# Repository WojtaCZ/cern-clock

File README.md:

# CERN CLOCK
This repository contains all the files for the CERN CLOCK project. The [firmware](firmware) folder contains the assembly for the 6809 processor as well as the sources for the RP Pico W. [Hardware](hardware) contains the reverse engineered schematic of the decoder board and the project for the controller board. [Mechanical](mechanical) folder contains the 3D printable parts and outlines for the plexi panels.

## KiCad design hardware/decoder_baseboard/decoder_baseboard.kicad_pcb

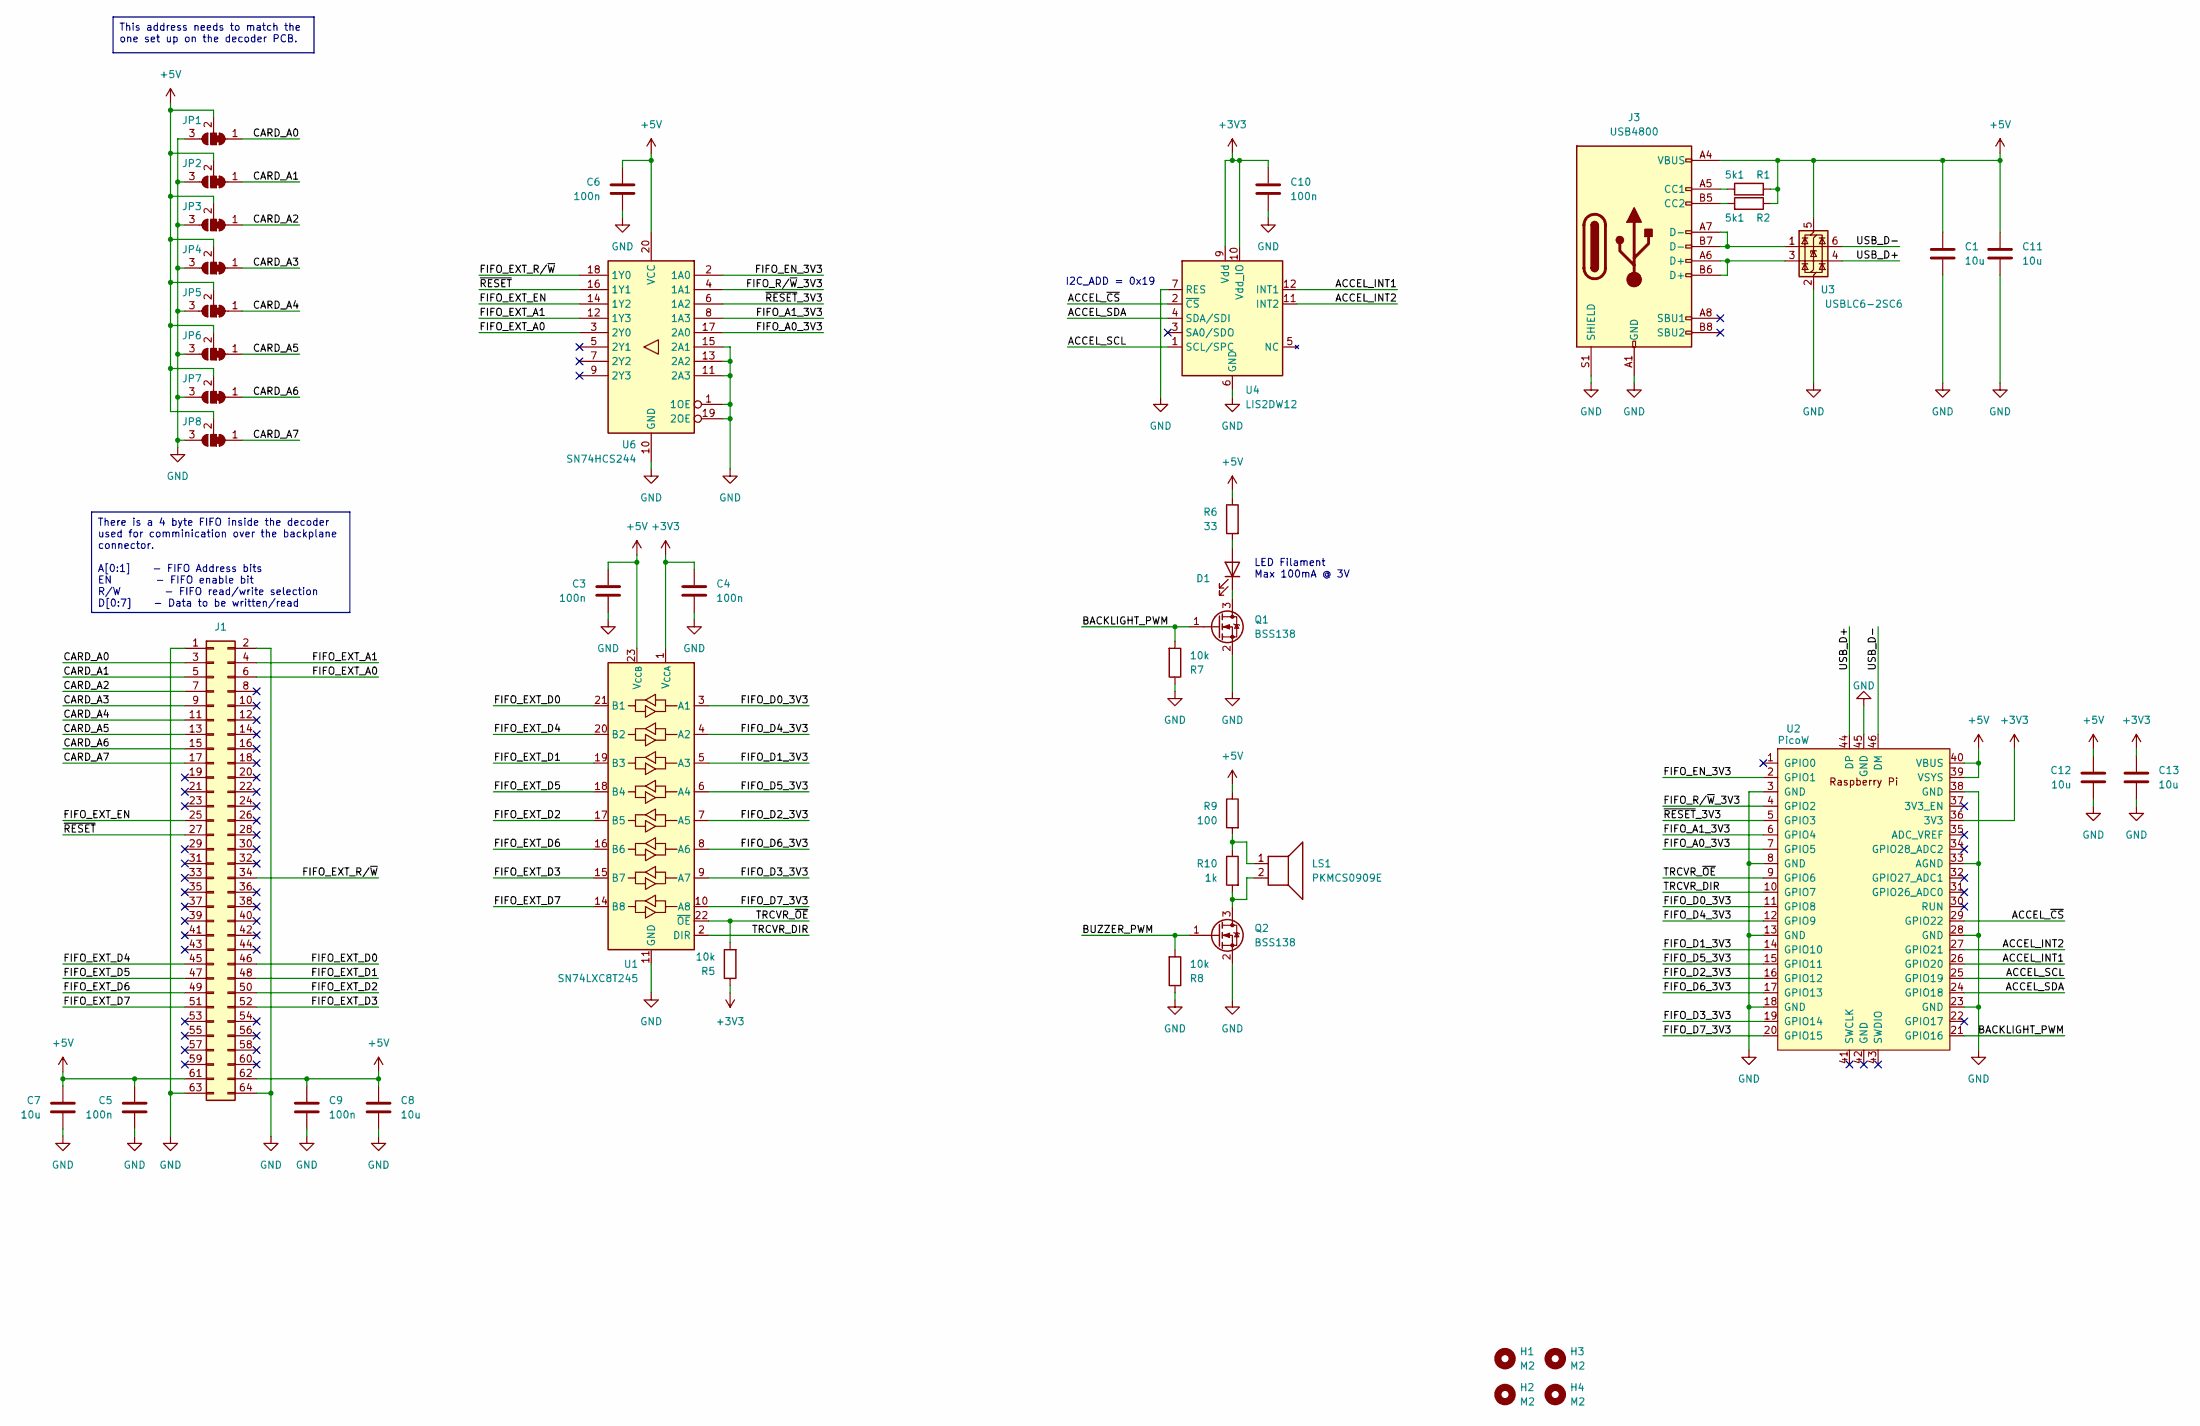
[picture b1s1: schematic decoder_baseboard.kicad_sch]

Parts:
C1, C7, C8, C11, C12, C13: 10u; C_0603_1608Metric
C3, C4, C5, C6, C9, C10: 100n; C_0603_1608Metric
D1: LED FILAMENT; Con_01x02_2.54_SMD
H1, H2, H3, H4: M2; MountingHole_2.5mm
J1: Conn_02x32_Odd_Even; PinSocket_2x32_P2.54mm_Vertical_SMD
J3: USB4800; USB_C_Receptacle_GCT_USB4800
JP1, JP2, JP3, JP4, JP5, JP6, JP7, JP8: SolderJumper_3_Bridged12; SolderJumper-3_P1.3mm_Bridged2Bar12_Pad1.0x1.5mm
LS1: PKMCS0909E; Buzzer_Murata_PKMCS0909E
Q1, Q2: BSS138; SOT-23
R1, R2: 5k1; R_0603_1608Metric
R5, R7, R8: 10k; R_0603_1608Metric
R6: 33; R_0603_1608Metric
R9: 100; R_0603_1608Metric
R10: 1k; R_0603_1608Metric
U1: SN74LXC8T245; TSSOP-24_4.4x7.8mm_P0.65mm
U2: PicoW; RPi_Pico_SMD_TH
U3: USBLC6-2SC6; SOT-23-6
U4: LIS2DW12; LGA-12_2x2mm_P0.5mm
U6: SN74HCS244; TSSOP-20_4.4x6.5mm_P0.65mm

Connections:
+3V3: C4.1, C10.1, C13.1, R5.1, U1.1 (V_{CCA}), U2.36 (3V3), U4.9 (Vdd), U4.10 (Vdd_IO)
+5V: C1.1, C3.1, C5.1, C6.1, C7.1, C8.1, C9.1, C11.1, C12.1, J1.61, J1.62, J3.A4 (VBUS), J3.A9 (VBUS), J3.B4 (VBUS), J3.B9 (VBUS), JP1.2 (C), JP2.2 (C), JP3.2 (C), JP4.2 (C), JP5.2 (C), JP6.2 (C), JP7.2 (C), JP8.2 (C), R1.2, R2.1, R6.1, R9.1, U1.23 (V_{CCB}), U1.24 (V_{CCB}), U2.39 (VSYS), U2.40 (VBUS), U3.5 (VBUS), U6.20 (VCC)
/ACCEL_INT1: U2.26 (GPIO20), U4.12 (INT1)
/ACCEL_INT2: U2.27 (GPIO21), U4.11 (INT2)
/ACCEL_SCL: U2.25 (GPIO19), U4.1 (SCL/SPC)
/ACCEL_SDA: U2.24 (GPIO18), U4.4 (SDA/SDI)
/ACCEL_~CS: U2.29 (GPIO22), U4.2 (~CS)
/BACKLIGHT_PWM: Q1.1 (G), R7.2, U2.21 (GPIO16)
/BUZZER_PWM: Q2.1 (G), R8.2
/CARD_A0: J1.3, JP1.1 (A)
/CARD_A1: J1.5, JP2.1 (A)
/CARD_A2: J1.7, JP3.1 (A)
/CARD_A3: J1.9, JP4.1 (A)
/CARD_A4: J1.11, JP5.1 (A)
/CARD_A5: J1.13, JP6.1 (A)
/CARD_A6: J1.15, JP7.1 (A)
/CARD_A7: J1.17, JP8.1 (A)
/FIFO_A0_3V3: U2.7 (GPIO5), U6.17 (2A0)
/FIFO_A1_3V3: U2.6 (GPIO4), U6.8 (1A3)
/FIFO_D0_3V3: U1.3 (A1), U2.11 (GPIO8)
/FIFO_D1_3V3: U1.5 (A3), U2.14 (GPIO10)
/FIFO_D2_3V3: U1.7 (A5), U2.16 (GPIO12)
/FIFO_D3_3V3: U1.9 (A7), U2.19 (GPIO14)
/FIFO_D4_3V3: U1.4 (A2), U2.12 (GPIO9)
/FIFO_D5_3V3: U1.6 (A4), U2.15 (GPIO11)
/FIFO_D6_3V3: U1.8 (A6), U2.17 (GPIO13)
/FIFO_D7_3V3: U1.10 (A8), U2.20 (GPIO15)
/FIFO_EN_3V3: U2.2 (GPIO1), U6.2 (1A0)
/FIFO_EXT_A0: J1.6, U6.3 (2Y0)
/FIFO_EXT_A1: J1.4, U6.12 (1Y3)
/FIFO_EXT_D0: J1.46, U1.21 (B1)
/FIFO_EXT_D1: J1.48, U1.19 (B3)
/FIFO_EXT_D2: J1.50, U1.17 (B5)
/FIFO_EXT_D3: J1.52, U1.15 (B7)
/FIFO_EXT_D4: J1.45, U1.20 (B2)
/FIFO_EXT_D5: J1.47, U1.18 (B4)
/FIFO_EXT_D6: J1.49, U1.16 (B6)
/FIFO_EXT_D7: J1.51, U1.14 (B8)
/FIFO_EXT_EN: J1.25, U6.14 (1Y2)
/FIFO_EXT_R/~W: J1.34, U6.18 (1Y0)
/FIFO_R/~W_3V3: U2.4 (GPIO2), U6.4 (1A1)
/TRCVR_DIR: U1.2 (DIR), U2.10 (GPIO7)
/TRCVR_~OE: R5.2, U1.22 (~OE), U2.9 (GPIO6)
/USB_D+: U2.44 (DP), U3.4 (I/O2)
/USB_D-: U2.46 (DM), U3.6 (I/O1)
/~RESET: J1.27, U6.16 (1Y1)
/~RESET_3V3: U2.5 (GPIO3), U6.6 (1A2)
GND: C1.2, C3.2, C4.2, C5.2, C6.2, C7.2, C8.2, C9.2, C10.2, C11.2, C12.2, C13.2, J1.1, J1.2, J1.63, J1.64, J3.A1 (GND), J3.A12 (GND), J3.B1 (GND), J3.B12 (GND), J3.S1 (SHIELD), JP1.3 (B), JP2.3 (B), JP3.3 (B), JP4.3 (B), JP5.3 (B), JP6.3 (B), JP7.3 (B), JP8.3 (B), Q1.2 (S), Q2.2 (S), R7.1, R8.1, U1.11 (GND), U1.12 (GND), U1.13 (GND), U2.3 (GND), U2.8 (GND), U2.13 (GND), U2.18 (GND), U2.23 (GND), U2.28 (GND), U2.33 (AGND), U2.38 (GND), U2.45 (GND), U3.2 (GND), U4.6 (GND), U4.7 (RES), U4.8 (GND), U6.1 (1OE), U6.10 (GND), U6.11 (2A3), U6.13 (2A2), U6.15 (2A1), U6.19 (2OE)
unnamed: D1.2 (A), R6.2
unnamed: D1.1 (K), Q1.3 (D)
unnamed: J3.A5 (CC1), R1.1
unnamed: J3.B5 (CC2), R2.2
unnamed: J3.A6 (D+), J3.B6 (D+), U3.3 (I/O2)
unnamed: J3.A7 (D-), J3.B7 (D-), U3.1 (I/O1)
unnamed: LS1.1, R9.2, R10.1
unnamed: LS1.2, Q2.3 (D), R10.2

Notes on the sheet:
This address needs to match the one set up on the decoder PCB.
There is a 4 byte FIFO inside the decoder used for comminication over the backplane connector. A[0:1] - FIFO Address bits EN - FIFO enable bit R/W - FIFO read/write selection D[0:7] - Data to be written/read
I2C_ADD = 0x19
LED Filament Max 100mA @ 3V

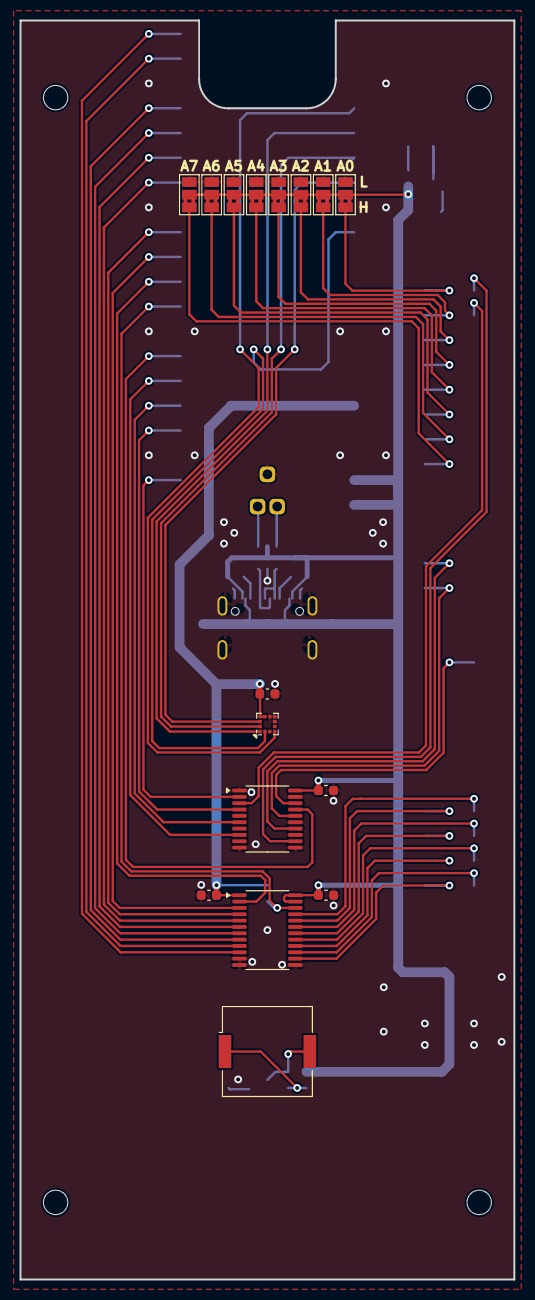
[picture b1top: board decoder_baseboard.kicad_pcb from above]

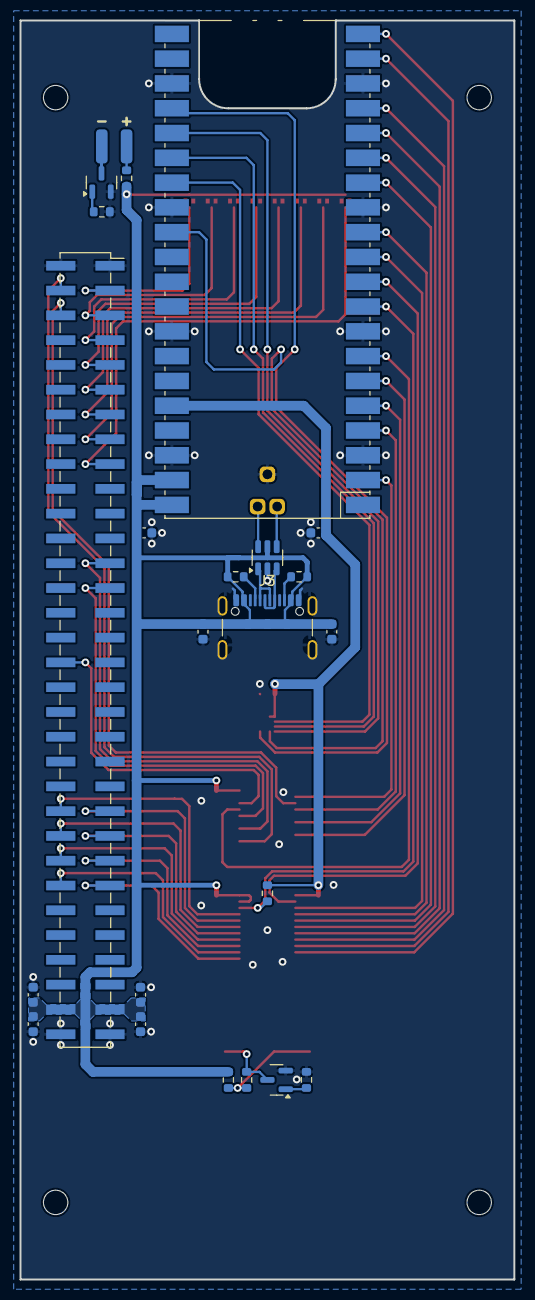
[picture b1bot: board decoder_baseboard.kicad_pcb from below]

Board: 2 copper layers, 50.6 x 129.0 mm, 43 parts (23 on the bottom side), 56 nets.

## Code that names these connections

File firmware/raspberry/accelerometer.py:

from machine import Pin
from machine import I2C
from machine import Timer
import time
import buzzer
import clock
import configuration
import ntp
import logging
logger = logging.getLogger(__name__)

tapCounterInternal = 0
tapCounter = 0
tapFlag = False
tapTimer = None

# Accelerometer interface
ACCEL_CSn		 = Pin(22, Pin.OUT, value=1)
ACCEL_INT1		 = Pin(20, Pin.IN)
ACCEL_INT2		 = Pin(21, Pin.IN)
ACCEL_SDA		 = Pin(18, Pin.PULL_UP)
ACCEL_SCL		 = Pin(19, Pin.PULL_UP)
ACCEL_I2C = I2C(1, freq=100000, scl=ACCEL_SCL, sda=ACCEL_SDA)
ACCEL_I2C_ADD = 25

overrideSleep = False

# Handle the finished tap procedure
def tapHandler(p):
    global tapCounterInternal, tapCounter, tapTimer, tapFlag
    
    # Kill the timer
    if tapTimer != None:
        tapTimer.deinit()
    
    # Update the vars
    tapCounter = tapCounterInternal
    tapCounterInternal = 0

    # Signal a finished tap for processing
    tapFlag = True
        
# If the tap interrupt was received
def int1_handler(p):
    global tapTimer, tapCounterInternal, overrideSleep
    
    # Beep
    buzzer.beep(600, 50)
    
    # Increase the tap count
    tapCounterInternal += 1

    # If the clock is not sleeping, behave ike a screen change
    timeNow = ntp.localTime()

    if (not clock.shouldSleep(timeNow)) or overrideSleep:
        # If it is the first tap, start a timer to wait for the possible second tap
        if tapCounterInternal == 1:
            tapTimer = Timer(period=600, mode=Timer.ONE_SHOT, callback=tapHandler)
        else:
            # Kill the timer and handle the taps
            if tapTimer != None:
                tapTimer.deinit()
            tapHandler(0)

    # But if it is sleeping, wake it up
    else:
        clock.wakeUp()
        return
    
# Set up the accel
def init():
    logger.debug("Initializing the accelerometer")
    
    if ACCEL_I2C.readfrom_mem(ACCEL_I2C_ADD, 0x0F, 1)[0] != 0x44:
        raise Exception("Wrong accelerometer ID!")
    
    logger.debug("Accelerometer detected. Setting up tap detection")
    
    # Set FS to 2g & enable lownoise
    ACCEL_I2C.writeto_mem(ACCEL_I2C_ADD, 0x25, b'\x04')
    # Tap detect routed to INT1
    ACCEL_I2C.writeto_mem(ACCEL_I2C_ADD, 0x23, b'\x40')
    
    # Tap tresholds & enabling
    tapEnableBits = 0; 
    tapEnabled = configuration.read("tap_enable_x");
    print(tapEnabled)
            
    if tapEnabled == "true":
        tapEnableBits |= 0x80
        logger.debug("Tap detection on X axis enabled.")
        try:
            tapTreshold = int(configuration.read("tap_treshold_x"))

            if tapTreshold > 31 or tapTreshold < 0:
                logger.warning("Tap treshold for X axis is out of limits, it will be constrained to comply with the limits")
                tapTreshold = max(min(31, tapTreshold, 0))
            
            logger.debug("Setting tap treshold for X axis to " + str(tapTreshold))
            ACCEL_I2C.writeto_mem(ACCEL_I2C_ADD, 0x30, tapTreshold.to_bytes(1))
        except:
            logger.warning("Tap treshold for X axis has not been found, even though tap detection is enabled. Setting to treshold 6")
            ACCEL_I2C.writeto_mem(ACCEL_I2C_ADD, 0x30, b'\x06')
    else:
        logger.debug("Tap detection on X axis disabled")
    
    tapEnabled = configuration.read("tap_enable_y")
     
    if tapEnabled == "true":
        tapEnableBits |= 0x40
        logger.debug("Tap detection on Y axis enabled")
        try:
            tapTreshold = int(configuration.read("tap_treshold_y"))
            
            if tapTreshold > 31 or tapTreshold < 0:
                logger.warning("Tap treshold for Y axis is out of limits, it will be constrained to comply with the limits")
                tapTreshold = max(min(31, tapTreshold, 0))
            
            logger.debug("Setting tap treshold for Y axis to " + str(tapTreshold))
            ACCEL_I2C.writeto_mem(ACCEL_I2C_ADD, 0x31, tapTreshold.to_bytes(1))
        except:
            logger.warning("Tap treshold for Y axis has not been found, even though tap detection is enabled. Setting to treshold 6")
            ACCEL_I2C.writeto_mem(ACCEL_I2C_ADD, 0x31, b'\x06')  
    else:
        logger.debug("Tap detection on Y axis disabled")
            
    tapEnabled = configuration.read("tap_enable_z")
    
    if tapEnabled == "true":
        tapEnableBits |= 0x20
        logger.debug("Tap detection on Z axis enabled.")
        try:
            tapTreshold = int(configuration.read("tap_treshold_z"))
            
            if tapTreshold > 31 or tapTreshold < 0:
                logger.warning("Tap treshold for Z axis is out of limits, it will be constrained to comply with the limits")
                tapTreshold = max(min(31, tapTreshold, 0))
            
            logger.debug("Setting tap treshold for Z axis to " + str(tapTreshold))
            ACCEL_I2C.writeto_mem(ACCEL_I2C_ADD, 0x32, (tapTreshold | tapEnableBits).to_bytes(1))
        except:
            logger.warning("Tap treshold for Z axis has not been found, even though tap detection is enabled. Setting to treshold 6")
            ACCEL_I2C.writeto_mem(ACCEL_I2C_ADD, 0x32,  (6 | tapEnableBits).to_bytes(1))     
    else:
        ACCEL_I2C.writeto_mem(ACCEL_I2C_ADD, 0x32,  tapEnableBits.to_bytes(1))
        logger.debug("Tap detection on Z axis disabled")
    
    # Set shock duration
    ACCEL_I2C.writeto_mem(ACCEL_I2C_ADD, 0x33, b'\x02')
    # Run mode @ 400Hz, high performance
    ACCEL_I2C.writeto_mem(ACCEL_I2C_ADD, 0x20, b'\x74')
    time.sleep(1)
    # Enable interrupts
    ACCEL_I2C.writeto_mem(ACCEL_I2C_ADD, 0x3F, b'\x20')
    
def enable():
    # Register accel interrupt
    ACCEL_INT1.irq(trigger=Pin.IRQ_RISING, handler=int1_handler)

def disable():
    # Unregister accel interrupt
    ACCEL_INT1.irq(trigger=Pin.IRQ_RISING, handler=None)

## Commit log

2024-05-26 Finished decoder board schematic
2024-06-23 Added display test program
2024-09-16 Added PICO footprint and USB
2024-09-17 Some routing done
2024-09-18 routing done
2024-09-18 sync
2024-10-01 finished rounded version
2024-10-29 Written the ASM file
2024-11-02 Got FW working
2024-11-03 Fixed some issues with the FW
2024-11-11 Added mechanical parts
2024-11-14 Got the network running
2024-11-14 Sockets not working for some reason
2024-11-30 Got vistars running
2024-12-02 Made decoder communication async
2024-12-08 Firmware seems to be working, but it's a mess
2024-12-09 Polished firmware files
2024-12-09 Added gitignore
2024-12-09 Moved gitignore
2024-12-09 Updated gitignore once again
2024-12-09 debugged minor errors
2024-12-09 fixed main
2024-12-10 Fixed sleeping
2024-12-14 Added logging module
2024-12-14 Cleaned
2024-12-14 Added tinyweb
2024-12-14 Added sample configuration
2025-04-30 Fix energy extraction
2025-04-30 Wakeup timer restart when vistars shows data
2025-04-30 Fixed tap timer
